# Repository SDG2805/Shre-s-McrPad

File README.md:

# Shre-s-McrPad
Hi, Everyone!
I'm Shreyas and with the help of Hack Club, have I designed a custom Macropad!

Here you can see it from a top down perspective:

Here you can take a look at my schematic for the Macropad which basically shows how the different components have to be connected.

In the following image you're able to look at the whole pcb!

The case and knobs are 3d-printed which will be assembled using screws for the upper and lower part of the body whilst the knobs will just fit on "rotary encoders".

And if you take a look at the bottom of the case, you can see 4 rectangular holes which are for the rbg-leds so that they can actually produce a visible lighting effect.

# BOM
Last but not least is my BOM (or Bill of Materials):
- 1x Seeed XIAO RP2040
- 9x Through-hole 1N4148 Diodes
- 9x MX-Style switches
- 2x EC11 Rotary encoders
- 9x Blank DSA keycaps (White)
- 4x SK6812 MINI-E LEDs
- 4x M3x16mm screws
- 4x M3x5mx4mm heatset inserts
- 2x 3d-printed knobs
- 1x 3d-printed case

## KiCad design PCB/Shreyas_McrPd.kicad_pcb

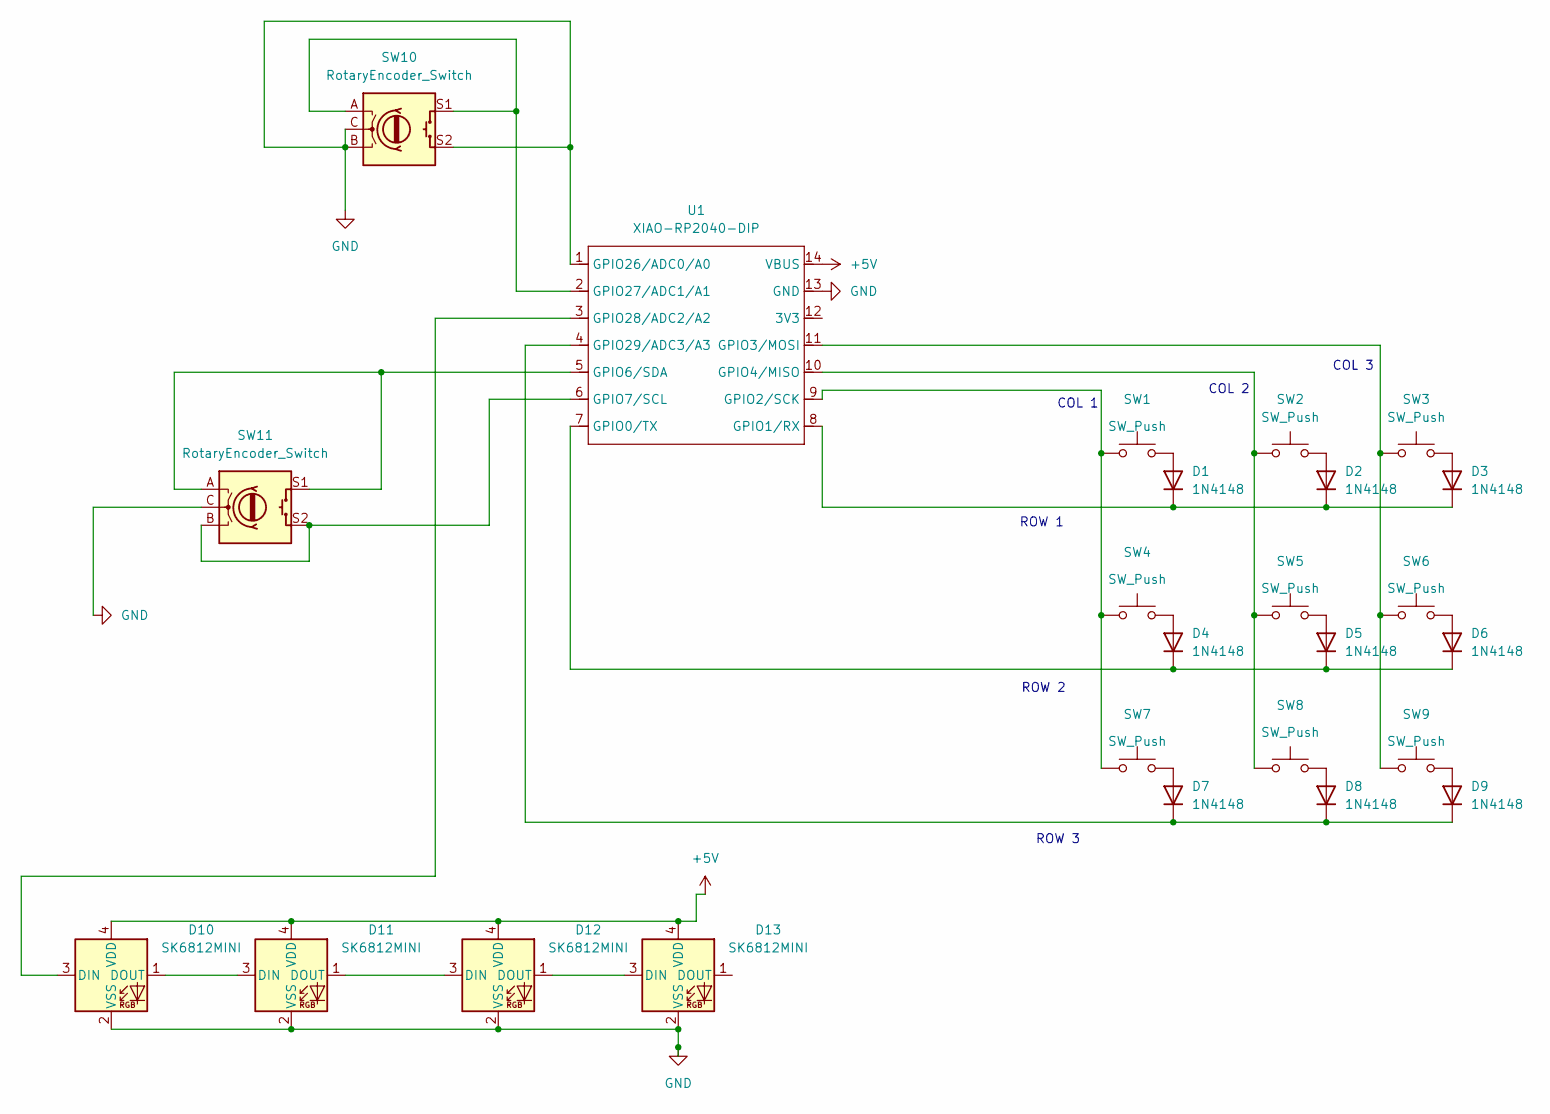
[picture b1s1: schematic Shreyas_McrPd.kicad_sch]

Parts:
D1, D2, D3, D4, D5, D6, D7, D8, D9: 1N4148; D_DO-35_SOD27_P7.62mm_Horizontal
D10, D11, D12, D13: SK6812MINI; LED_SK6812MINI_PLCC4_3.5x3.5mm_P1.75mm
SW1, SW2, SW3, SW4, SW5, SW6, SW7, SW8, SW9: SW_Push; SW_Cherry_MX_1.00u_PCB
SW10, SW11: RotaryEncoder_Switch; RotaryEncoder_Alps_EC11E-Switch_Vertical_H20mm
U1: XIAO-RP2040-DIP

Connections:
+5V: D10.4 (VDD), D11.4 (VDD), D12.4 (VDD), D13.4 (VDD), U1.14 (VBUS)
unnamed: D1.2 (A), SW1.2
unnamed: D1.1 (K), D2.1 (K), D3.1 (K), U1.8 (GPIO1/RX)
unnamed: D2.2 (A), SW2.2
unnamed: D3.2 (A), SW3.2
unnamed: D4.2 (A), SW4.1
unnamed: D4.1 (K), D5.1 (K), D6.1 (K), U1.7 (GPIO0/TX)
unnamed: D5.2 (A), SW5.2
unnamed: D6.2 (A), SW6.2
unnamed: D7.2 (A), SW7.2
unnamed: D7.1 (K), D8.1 (K), D9.1 (K), U1.4 (GPIO29/ADC3/A3)
unnamed: D8.2 (A), SW8.1
unnamed: D9.2 (A), SW9.2
unnamed: D10.3 (DIN), U1.3 (GPIO28/ADC2/A2)
unnamed: D10.1 (DOUT), D11.3 (DIN)
unnamed: D11.1 (DOUT), D12.3 (DIN)
unnamed: D12.1 (DOUT), D13.3 (DIN)
unnamed: SW1.1, SW4.2, SW7.1, U1.9 (GPIO2/SCK)
unnamed: SW3.1, SW6.1, SW9.1, U1.11 (GPIO3/MOSI)
unnamed: SW2.1, SW5.1, SW8.2, U1.10 (GPIO4/MISO)
unnamed: SW11.A, SW11.S1, U1.5 (GPIO6/SDA)
unnamed: SW11.B, SW11.S2, U1.6 (GPIO7/SCL)
unnamed: SW10.A, SW10.S1, U1.2 (GPIO27/ADC1/A1)

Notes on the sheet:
ROW 2
COL 3
COL 1
COL 2
ROW 3
ROW 1

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
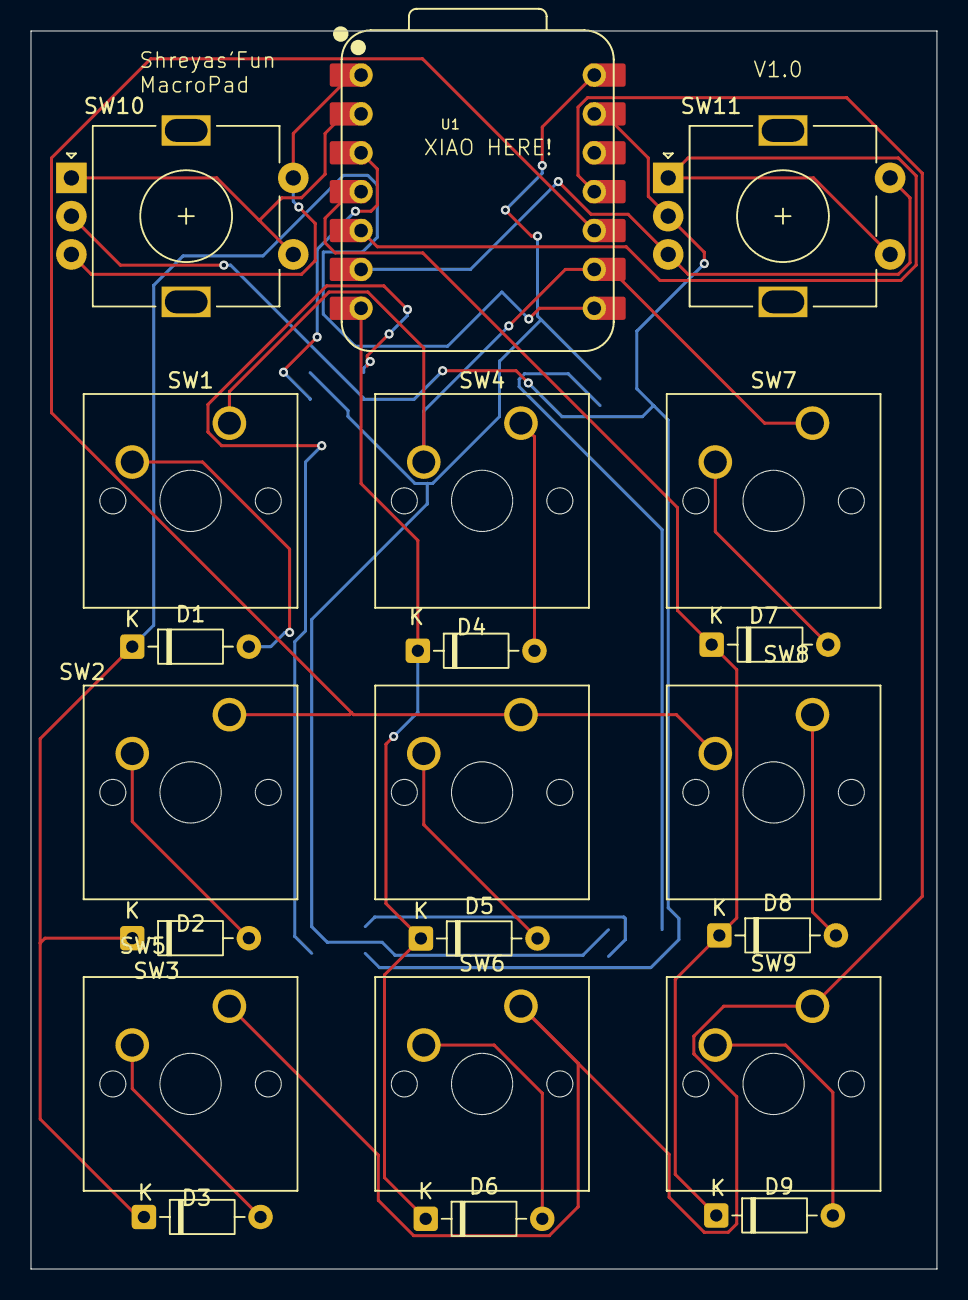
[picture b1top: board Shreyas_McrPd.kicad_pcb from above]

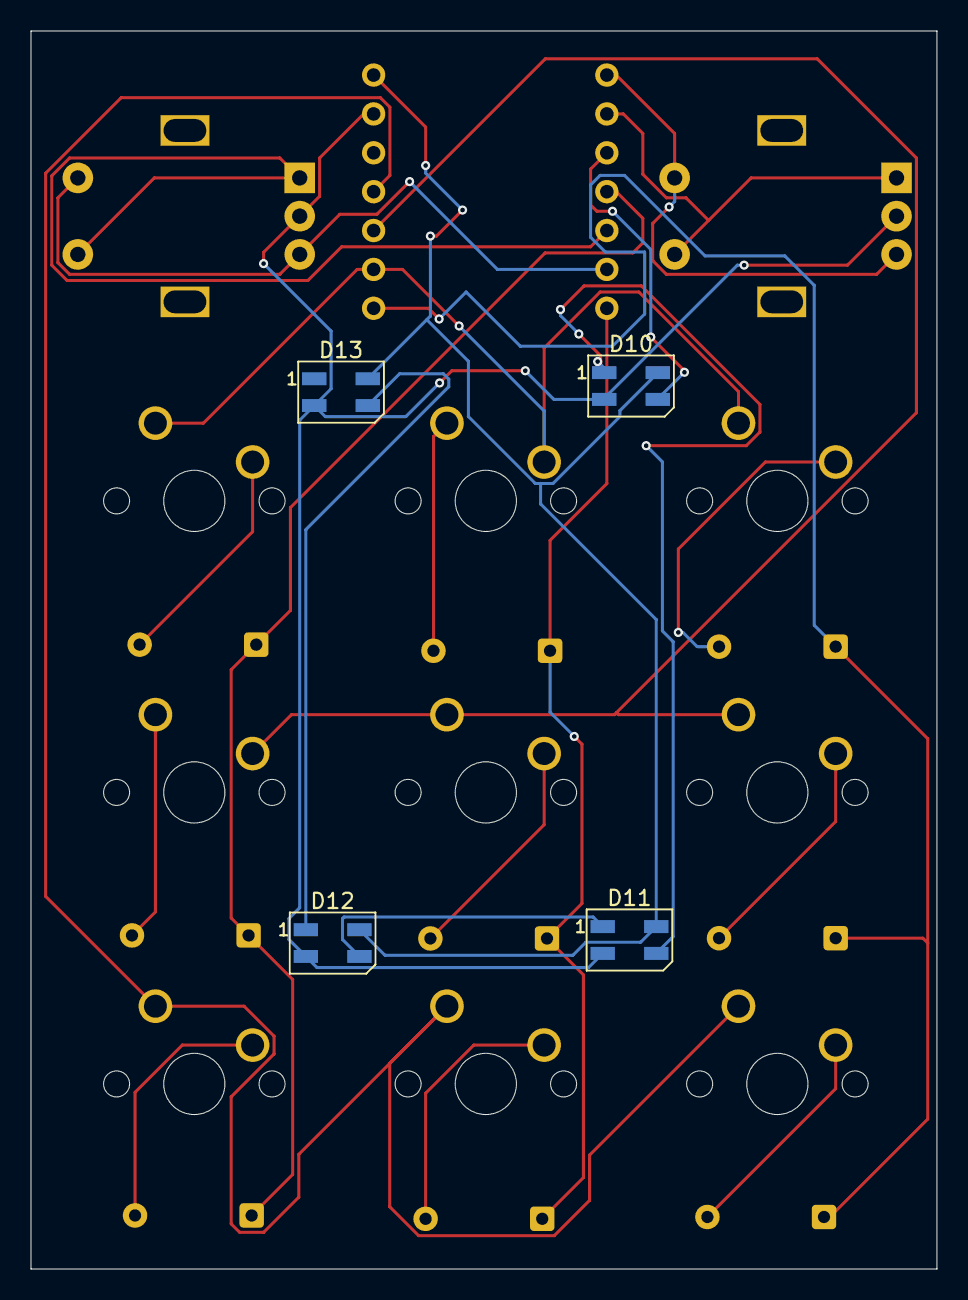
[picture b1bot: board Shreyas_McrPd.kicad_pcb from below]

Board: 2 copper layers, 59.2 x 80.9 mm, 25 parts (4 on the bottom side), 25 nets.

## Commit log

2026-01-01 Create temp
2026-01-01 Create t
